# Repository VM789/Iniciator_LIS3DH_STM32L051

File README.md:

## About
IMP (Initiator Martynov & Pivovarov) is an ultra-low-power electronic initiator based on the STM32L0 microcontroller, designed specifically for drone applications.

## Key Features
Dual Activation Methods:

Ultra-sensitive 3-axis tilt and vibration detection

Programmable timer with a lifespan of up to two years

## Exceptional Power Efficiency:

Designed to operate from standard batteries (CR2450, MN27)

Sleep mode current consumption: as low as 3.5 µA

Estimated battery life with CR2450: over 7 years (calculated)

## Robust Operation:

Recommended operating temperature: below 60°C

Short-term tolerance: up to 80°C

Dual-stage protection circuitry for enhanced safety and reliability in diverse environments

## Purpose
IMP serves as a prototype/research platform for developing, testing, and educational projects in the UAV domain. Its architecture emphasizes extreme energy efficiency through advanced low-power modes.

⚠️ Important Notice: This project is intended for civilian, research, and educational purposes only. Always adhere to local laws and safety regulations when working with UAV components.
## Documentation

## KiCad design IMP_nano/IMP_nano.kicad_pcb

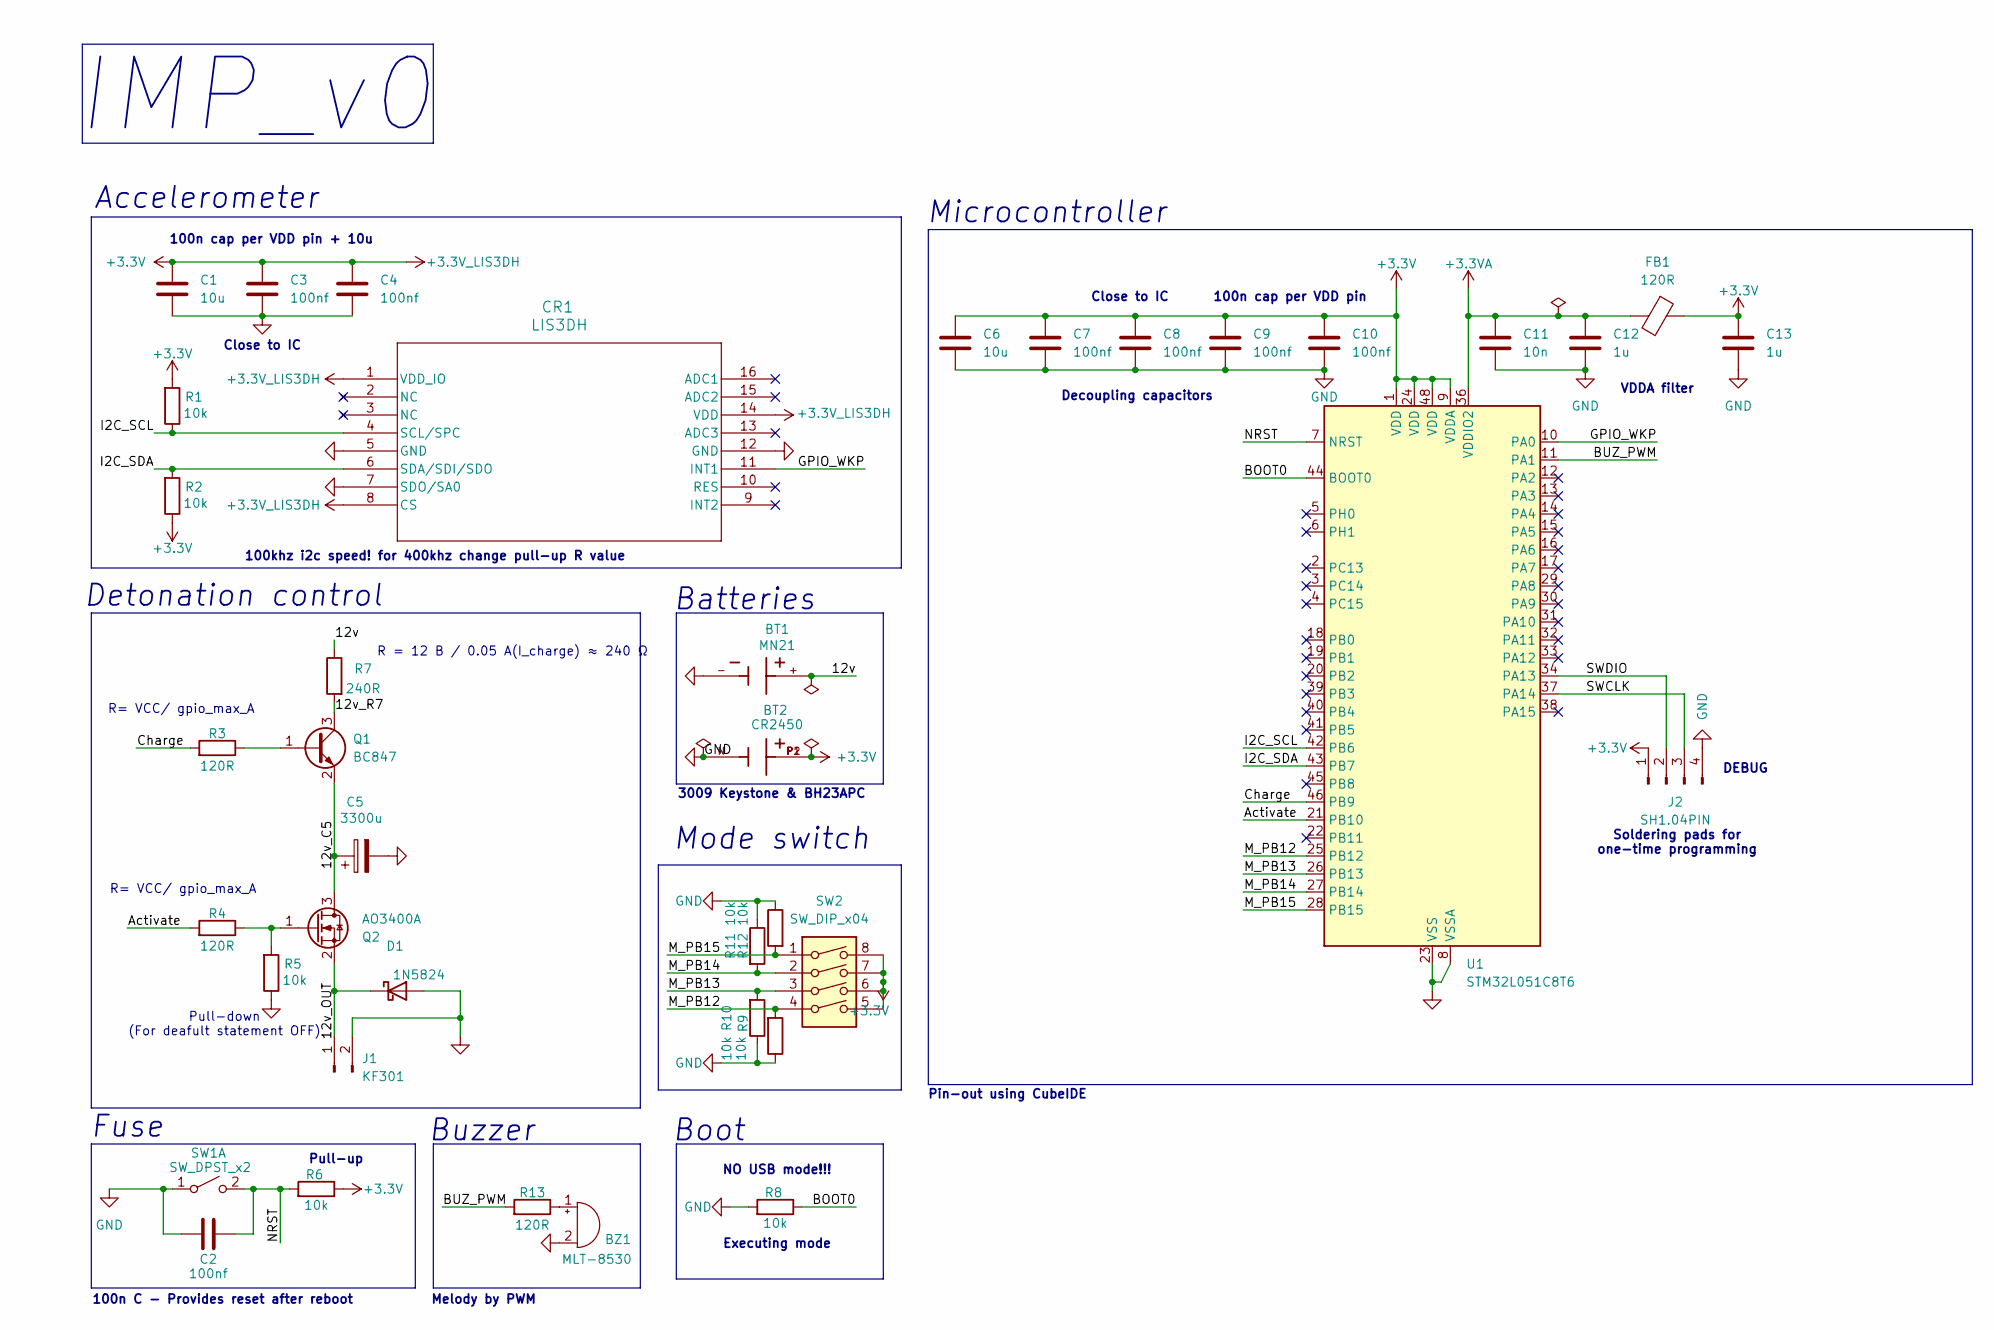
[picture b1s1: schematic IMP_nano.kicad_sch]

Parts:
BT1: MN21; BAT_BH23APC; PARTREV K
BT2: CR2450; BAT_3009; PARTREV G
BZ1: MLT-8530; MLT-8530_JHE
C1, C6: 10u; C_0201_0603Metric
C2, C3, C4, C7, C8, C9, C10: 100nf; C_0201_0603Metric
C5: 3300u; CP_Radial_D13.0mm_P5.00mm
C11: 10n; C_0201_0603Metric
C12, C13: 1u; C_0201_0603Metric
CR1: LIS3DH; LGA-16_3x3mm_P0.5mm
D1: 1N5824; D_SMA
FB1: 120R; L_0201_0603Metric
J1: KF301; HANDSON_KF301-2P
J2: SH1.04PIN; JST_SH_SM04B-SRSS-TB_1x04-1MP_P1.00mm_Horizontal
Q1: BC847; SOT-23
Q2: AO3400A; SOT-23
R1, R2, R5, R6, R8, R9, R10, R11, R12: 10k; R_0201_0603Metric
R3, R4, R13: 120R; R_0201_0603Metric
R7: 240R; RESC6432X90N
SW1: SW_DPST_x2; SW_XKB_DM1-16UP-1
SW2: SW_DIP_x04; SW_A6S-4101-H_OMR
U1: STM32L051C8T6; LQFP-48_7x7mm_P0.5mm

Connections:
+3.3V: BT2.P1, BT2.P2, C1.1, C3.1, C4.1, C6.1, C7.1, C8.1, C9.1, C10.1, C13.1, CR1.1 (VDD_IO), CR1.8 (CS), CR1.14 (VDD), FB1.1, J2.1, R1.2, R2.1, R6.1, SW2.5, SW2.6, SW2.7, SW2.8, U1.1 (VDD), U1.9 (VDDA), U1.24 (VDD), U1.48 (VDD)
+3.3VA: C11.1, C12.1, FB1.2, U1.36 (VDDIO2)
/12v: BT1.+, R7.1
/12v_C5: C5.1, Q1.2 (E), Q2.3 (D)
/12v_OUT: D1.1 (K), J1.1, Q2.2 (S)
/12v_R7: Q1.3 (C), R7.2
/Activate: R4.2, U1.21 (PB10)
/BOOT0: R8.1, U1.44 (BOOT0)
/BUZ_PWM: R13.2, U1.11 (PA1)
/Charge: R3.2, U1.46 (PB9)
/GPIO_WKP: CR1.11 (INT1), U1.10 (PA0)
/I2C_SCL: CR1.4 (SCL/SPC), R1.1, U1.42 (PB6)
/I2C_SDA: CR1.6 (SDA/SDI/SDO), R2.2, U1.43 (PB7)
/M_PB12: R9.2, SW2.4, U1.25 (PB12)
/M_PB13: R10.2, SW2.3, U1.26 (PB13)
/M_PB14: R11.2, SW2.2, U1.27 (PB14)
/M_PB15: R12.2, SW2.1, U1.28 (PB15)
/NRST: C2.2, R6.2, SW1.2 (B), U1.7 (NRST)
/SWCLK: J2.3, U1.37 (PA14)
/SWDIO: J2.2, U1.34 (PA13)
GND: BT1.-, BT2.N, BZ1.2 (-), C1.2, C2.1, C3.2, C4.2, C5.2, C6.2, C7.2, C8.2, C9.2, C10.2, C11.2, C12.2, C13.2, CR1.5 (GND), CR1.7 (SDO/SA0), CR1.12 (GND), D1.2 (A), J1.2, J2.4, R5.1, R8.2, R9.1, R10.1, R11.1, R12.1, SW1.1 (A), U1.8 (VSSA), U1.23 (VSS), U1.35 (VSS), U1.47 (VSS)
unnamed: BZ1.1 (+), R13.1
unnamed: Q1.1 (B), R3.1
unnamed: Q2.1 (G), R4.1, R5.2

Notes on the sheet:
IMP_v0
DEBUG
Accelerometer
Melody by PWM
R= VCC/ gpio_max_A
R = 12 В / 0.05 А(I_charge) ≈ 240 Ω
Pull-up
Decoupling capacitors
Mode switch
100khz i2c speed! for 400khz change pull-up R value
Soldering pads for one-time programming
Detonation control
Boot
Executing mode
Pin-out using CubeIDE
NO USB mode!!!
100n cap per VDD pin
Buzzer
3009 Keystone & BH23APC
Fuse
Batteries
VDDA filter
100n cap per VDD pin + 10u
Close to IC
100n C - Provides reset after reboot
Pull-down (For deafult statement OFF)
Microcontroller

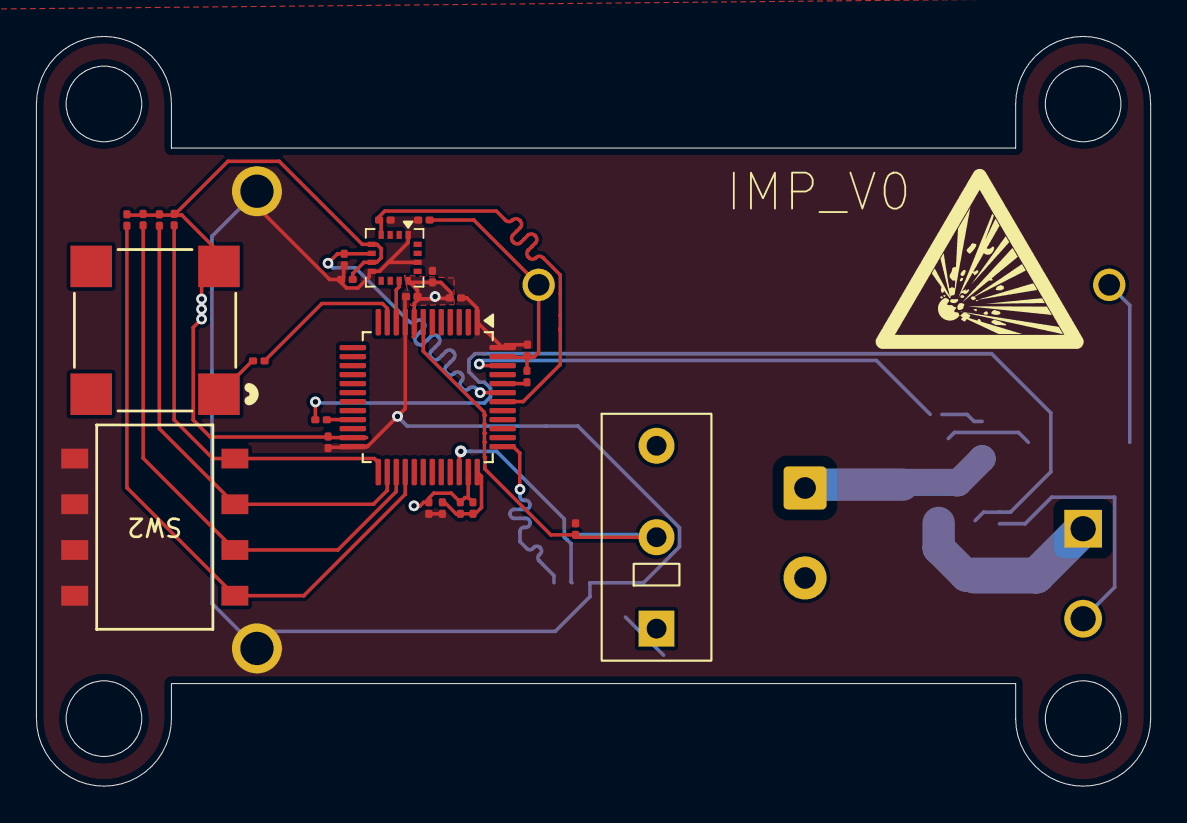
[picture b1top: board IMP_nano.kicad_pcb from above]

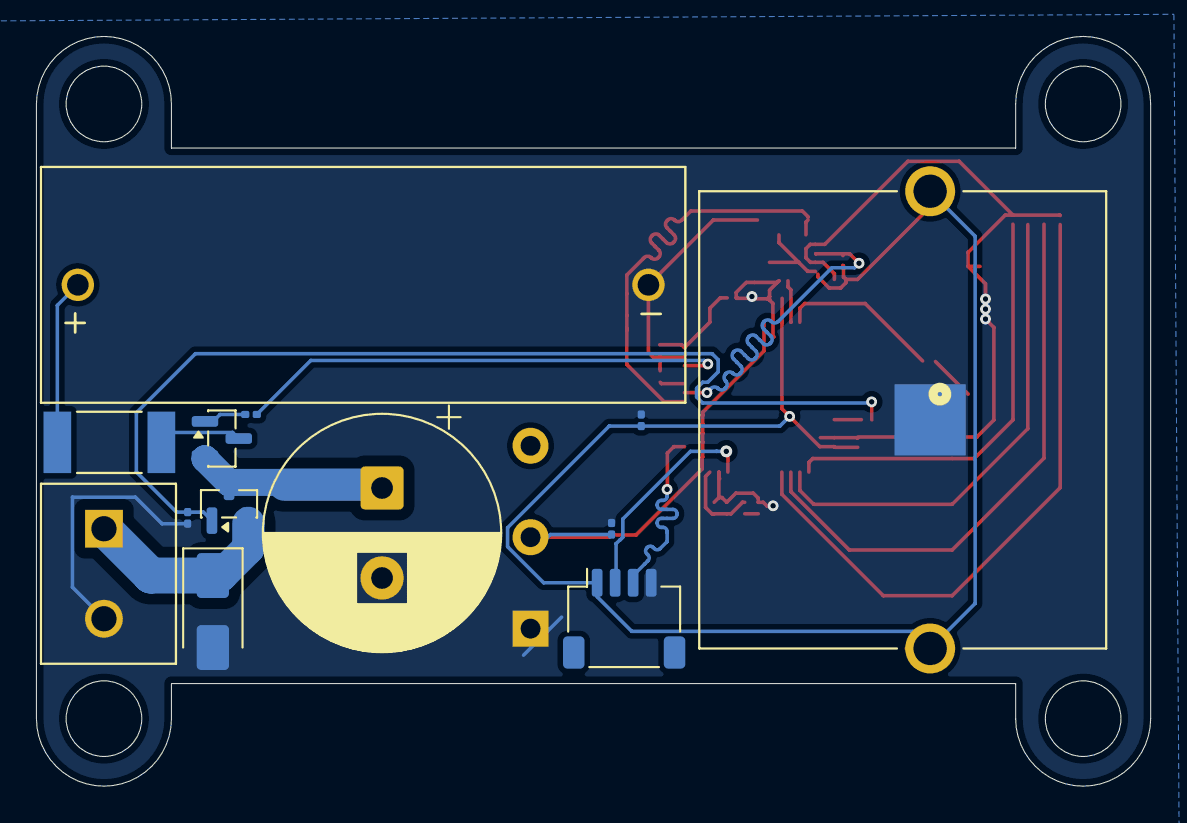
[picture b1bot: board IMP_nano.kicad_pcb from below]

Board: 2 copper layers, 61.9 x 41.6 mm, 39 parts (13 on the bottom side), 24 nets.

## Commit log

2026-01-21 Initial README commit
    -Added detailed project description, features, and documentation.
    -21/1/26
2026-01-21 schematic intial
2026-01-23 Schematic update + footprint assignment + 3d models
    -Buzzer added
    -23/1/26
2026-01-24 precomplete of back side of pcb
2026-01-26 PCB - placed all components - added filled copper zones(back - GND, front - 3v3) SCHEMATIC - corrected mode switch
2026-01-27 Small schematic edition
    -27/1/26
2026-01-27 Revert "Small schematic edition"
    This reverts commit bbe39c2e898aba73dfbb216a0e94a96616dd3fc8.
2026-01-27 Revert "Merge branch 'main' of https://github.com/VM789/Iniciator_LIS3DH_STM32L051"
    This reverts commit 2288a0702c7a77f2620ef9b25b47770eba569139, reversing
    changes made to 1a90470a2cd177be53fc6e450877d8afaef4cfb5.
2026-01-27 Reapply "Merge branch 'main' of https://github.com/VM789/Iniciator_LIS3DH_STM32L051"
    This reverts commit 2ad7139c444b11e79b7e6934f4438ad5f06415cd.
2026-01-27 Revert "Reapply "Merge branch 'main' of https://github.com/VM789/Iniciator_LIS3DH_STM32L051""
    This reverts commit 233d6eef3dcd649c9f04f6cd4fccbee5f65a1196.
2026-01-27 update pcb & schematic
2026-01-28 Remove documentation section from README
    Removed the documentation section and its associated image.
2026-01-28 fully made pcb & update schematic
2026-01-30 No DRC errors on pcb
2026-01-30 Sigh and picture added to pcb
2026-01-30 3D models added
2026-01-31 Zip gerber added
2026-02-01 Schematic cleaning, reviewed be me
2026-02-01 Revert "Merge branch 'main' into dev"
    This reverts commit 4bfed35f0fa768d1f404c50a8014cad2842e3d8f, reversing
    changes made to adbaa71b36a26864ecb25a24bcb0671c29aebaac.
2026-02-01 GERBER and Zip added
2026-02-01 Cleaning
2026-02-01 corrected pcb & schematic
2026-02-01 Add .gitignore
2026-04-26 Fix formatting in README documentation section
2026-05-07 Shematic update by VM
    Iniciation shrmatic editing

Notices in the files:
README.md:
License: IDK
